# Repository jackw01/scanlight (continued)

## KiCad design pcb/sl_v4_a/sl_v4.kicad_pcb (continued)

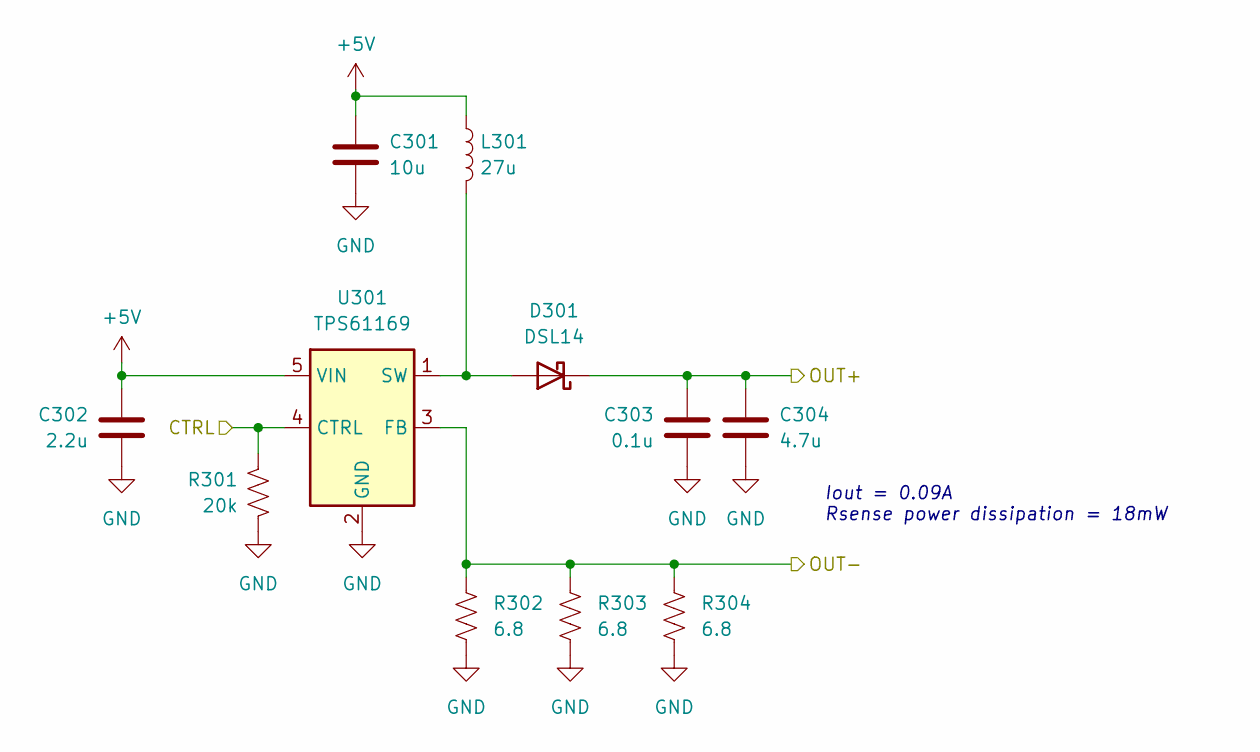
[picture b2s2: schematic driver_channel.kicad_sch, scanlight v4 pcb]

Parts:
C301: 10u; C_0805_2012Metric; MPN CL21A106KAYNNNE; LCSC C15850
C302: 2.2u; C_0402_1005Metric; MPN CL05A225MQ5NSNC; LCSC C12530
C303: 0.1u; C_0402_1005Metric; MPN CL05B104KB54PNC; LCSC C307331
C304: 4.7u; C_1206_3216Metric; MPN 1206B475K500NT; LCSC C29823
D301: DSL14; D_SOD-123F; MPN DSL14; LCSC C22466349
L301: 27u; L_Sunlord_SWPA6028S; MPN CR6028-270M; LCSC C7588756
R301: 20k; R_0402_1005Metric; MPN 0402WGF2002TCE; LCSC C25765
R302, R303, R304: 6.8; R_0402_1005Metric; MPN AC0402FR-076R8L; LCSC C227211
U301: TPS61169; SOT-353_SC-70-5; MPN TPS61169DCKR; LCSC C71045

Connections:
+5V: C301.1, C302.1, L301.1, U301.5 (VIN); also elsewhere on the board
/R1: R301.1, U301.4 (CTRL); also elsewhere on the board
/R1+: C303.1, C304.1, D301.1 (K); also elsewhere on the board
/R1-: R302.1, R303.1, R304.1, U301.3 (FB); also elsewhere on the board
GND: C301.2, C302.2, C303.2, C304.2, R301.2, R302.2, R303.2, R304.2, U301.2 (GND); also elsewhere on the board
unnamed: D301.2 (A), L301.2, U301.1 (SW)

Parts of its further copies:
C401, C501, C601: 10u; C_0805_2012Metric; MPN CL21A106KAYNNNE; LCSC C15850
C402, C502, C602: 2.2u; C_0402_1005Metric; MPN CL05A225MQ5NSNC; LCSC C12530
C403, C503, C603: 0.1u; C_0402_1005Metric; MPN CL05B104KB54PNC; LCSC C307331
C404, C504, C604: 4.7u; C_1206_3216Metric; MPN 1206B475K500NT; LCSC C29823
D401, D501, D601: DSL14; D_SOD-123F; MPN DSL14; LCSC C22466349
L401, L501, L601: 27u; L_Sunlord_SWPA6028S; MPN CR6028-270M; LCSC C7588756
R401, R501, R601: 20k; R_0402_1005Metric; MPN 0402WGF2002TCE; LCSC C25765
R402, R403, R404, R502, R503, R504, R602, R603, R604: 6.8; R_0402_1005Metric; MPN AC0402FR-076R8L; LCSC C227211
U401, U501, U601: TPS61169; SOT-353_SC-70-5; MPN TPS61169DCKR; LCSC C71045

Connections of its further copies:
+5V: C401.1, C402.1, C501.1, C502.1, C601.1, C602.1, L401.1, L501.1, L601.1, U401.5 (VIN), U501.5 (VIN), U601.5 (VIN); also elsewhere on the board
/B1: R501.1, U501.4 (CTRL); also elsewhere on the board
/B1+: C503.1, C504.1, D501.1 (K); also elsewhere on the board
/B1-: R502.1, R503.1, R504.1, U501.3 (FB); also elsewhere on the board
/G1: R401.1, U401.4 (CTRL); also elsewhere on the board
/G1+: C403.1, C404.1, D401.1 (K); also elsewhere on the board
/G1-: R402.1, R403.1, R404.1, U401.3 (FB); also elsewhere on the board
/W1: R601.1, U601.4 (CTRL); also elsewhere on the board
/W1+: C603.1, C604.1, D601.1 (K); also elsewhere on the board
/W1-: R602.1, R603.1, R604.1, U601.3 (FB); also elsewhere on the board
GND: C401.2, C402.2, C403.2, C404.2, C501.2, C502.2, C503.2, C504.2, C601.2, C602.2, C603.2, C604.2, R401.2, R402.2, R403.2, R404.2, R501.2, R502.2, R503.2, R504.2, R601.2, R602.2, R603.2, R604.2, U401.2 (GND), U501.2 (GND), U601.2 (GND); also elsewhere on the board
unnamed: D401.2 (A), L401.2, U401.1 (SW)
unnamed: D501.2 (A), L501.2, U501.1 (SW)
unnamed: D601.2 (A), L601.2, U601.1 (SW)

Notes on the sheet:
Iout = 0.09A Rsense power dissipation = 18mW

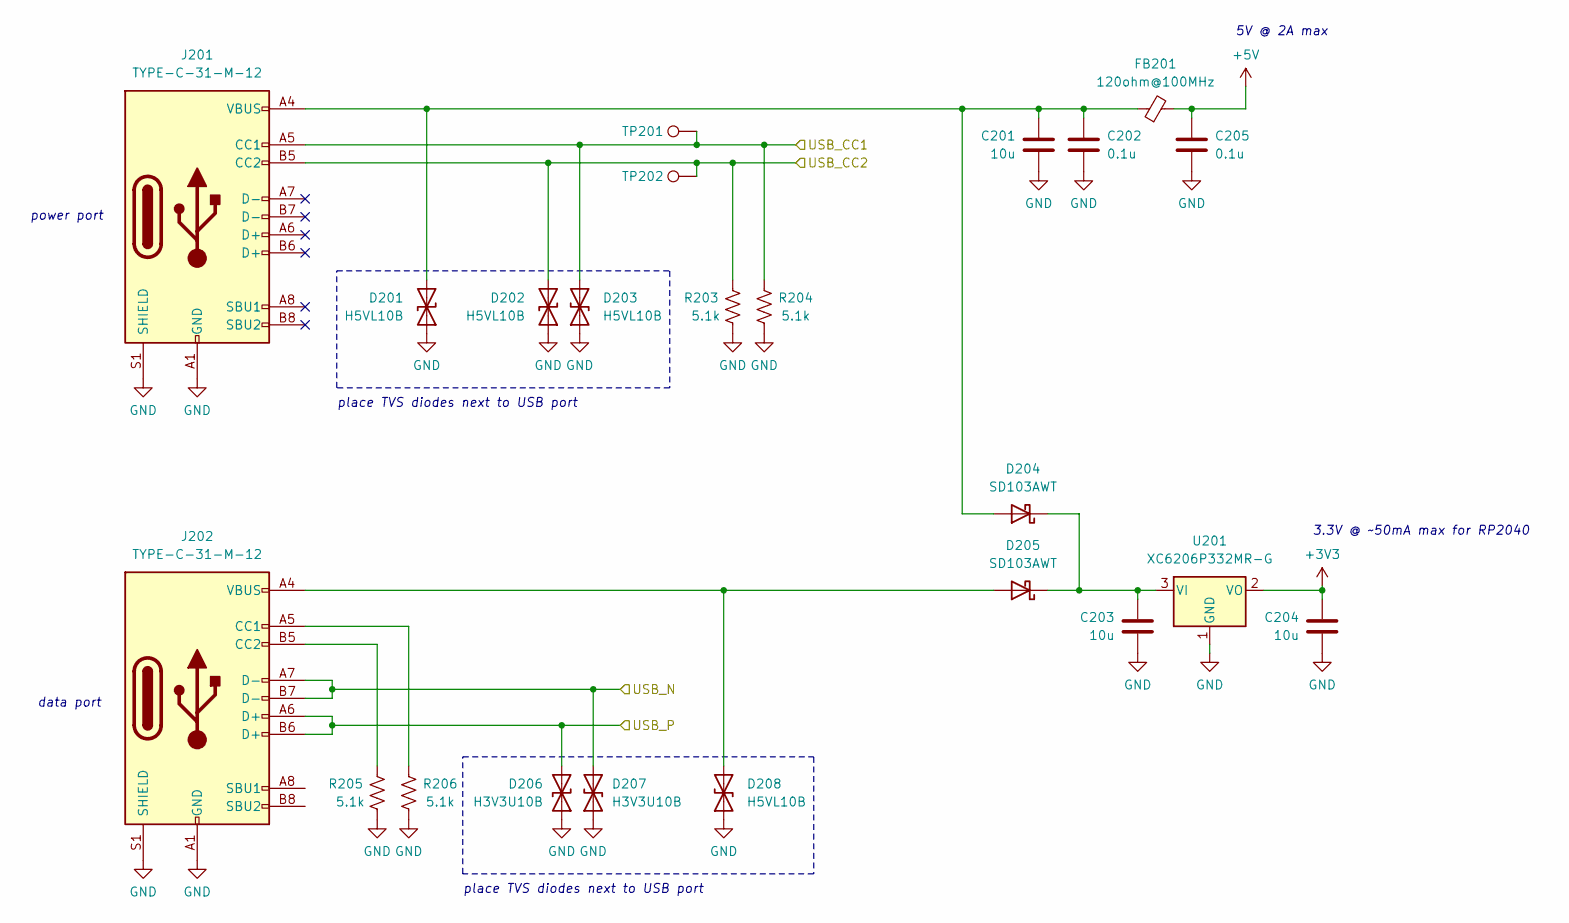
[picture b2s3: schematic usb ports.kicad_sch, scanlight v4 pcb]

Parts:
C201, C203, C204: 10u; C_0805_2012Metric; MPN CL21A106KAYNNNE; LCSC C15850
C202, C205: 0.1u; C_0402_1005Metric; MPN CL05B104KB54PNC; LCSC C307331
D201, D202, D203, D208: H5VL10B; D_SOD-882; MPN H5VL10B; LCSC C7420372
D204, D205: SD103AWT; D_SOD-523; MPN SD103AWT; LCSC C22466357
D206, D207: H3V3U10B; D_SOD-882; MPN H3V3U10B; LCSC C20615782
FB201: 120ohm@100MHz; L_0805_2012Metric; MPN UPZ2012E121-4R0TF; LCSC C97001
J201, J202: TYPE-C-31-M-12; USB_C_Receptacle_HRO_TYPE-C-31-M-12; MPN TYPE-C-31-M-12; LCSC C165948
R203, R204, R205, R206: 5.1k; R_0402_1005Metric; MPN 0402WGF5101TCE; LCSC C25905
TP201, TP202: TestPoint; TestPoint_Pad_D1.0mm
U201: XC6206P332MR-G; SOT-23-3; MPN XC6206P332MR-G; LCSC C5446

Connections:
+3V3: C204.1, U201.2 (VO); also elsewhere on the board
+5V: C205.1, FB201.2; also elsewhere on the board
/CC1: D203.2 (A2), J201.A5 (CC1), R204.1, TP201.1 (1_1); also elsewhere on the board
/CC2: D202.2 (A2), J201.B5 (CC2), R203.2, TP202.1 (1_1); also elsewhere on the board
/usb ports/USB_N: D207.2 (A2), J202.A7 (D-), J202.B7 (D-); also elsewhere on the board
/usb ports/USB_P: D206.2 (A2), J202.A6 (D+), J202.B6 (D+); also elsewhere on the board
GND: C201.2, C202.2, C203.2, C204.2, C205.2, D201.1 (A1), D202.1 (A1), D203.1 (A1), D206.1 (A1), D207.1 (A1), D208.1 (A1), J201.A1 (GND), J201.A12 (GND), J201.B1 (GND), J201.B12 (GND), J201.S1 (SHIELD), J202.A1 (GND), J202.A12 (GND), J202.B1 (GND), J202.B12 (GND), J202.S1 (SHIELD), R203.1, R204.2, R205.1, R206.2, U201.1 (GND); also elsewhere on the board
unnamed: C201.1, C202.1, D201.2 (A2), D204.2 (A), FB201.1, J201.A4 (VBUS), J201.A9 (VBUS), J201.B4 (VBUS), J201.B9 (VBUS)
unnamed: C203.1, D204.1 (K), D205.1 (K), U201.3 (VI)
unnamed: D205.2 (A), D208.2 (A2), J202.A4 (VBUS), J202.A9 (VBUS), J202.B4 (VBUS), J202.B9 (VBUS)
unnamed: J202.A5 (CC1), R206.1
unnamed: J202.B5 (CC2), R205.2

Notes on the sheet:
place TVS diodes next to USB port
power port
5V @ 2A max
3.3V @ ~50mA max for RP2040
data port

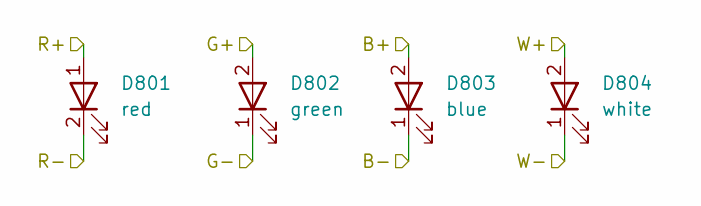
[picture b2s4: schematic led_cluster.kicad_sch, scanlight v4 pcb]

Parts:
D801: red; LED_2835_Reversed_Red_compact; MPN HL-AS-2835D15FC-S1-08-PCT-ZW-P6; LCSC C49435764
D802: green; LED_2835_compact; MPN TJ-S2835UG5W8TLC2G-A5; LCSC C440451
D803: blue; LED_2835_compact; MPN TJ-S2835UG5W8TLC6B-A5; LCSC C440452
D804: white; LED_2835_compact; MPN HL-AM-2835H421W-S1-08-HR6(SDCM<6)(4750K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; LCSC C516133

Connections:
/B1+: D803.2 (A); also elsewhere on the board
/G1+: D802.2 (A); also elsewhere on the board
/LED array/LED Cluster 0/B-: D803.1 (K); also elsewhere on the board
/LED array/LED Cluster 0/G-: D802.1 (K); also elsewhere on the board
/LED array/LED Cluster 0/R-: D801.2 (K); also elsewhere on the board
/LED array/LED Cluster 0/W-: D804.1 (K); also elsewhere on the board
/R1+: D801.1 (A); also elsewhere on the board
/W1+: D804.2 (A); also elsewhere on the board

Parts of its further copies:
D901, D1001, D1101, D1201, D1301, D1401, D1501, D1601: red; LED_2835_Reversed_Red_compact; MPN HL-AS-2835D15FC-S1-08-PCT-ZW-P6; LCSC C49435764
D902, D1002, D1102, D1202, D1302, D1402, D1502, D1602: green; LED_2835_compact; MPN TJ-S2835UG5W8TLC2G-A5; LCSC C440451
D903, D1003, D1103, D1203, D1303, D1403, D1503, D1603: blue; LED_2835_compact; MPN TJ-S2835UG5W8TLC6B-A5; LCSC C440452
D904, D1004, D1104, D1204, D1304, D1404, D1504, D1604: white; LED_2835_compact; MPN HL-AM-2835H421W-S1-08-HR6(SDCM<6)(4750K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; LCSC C516133

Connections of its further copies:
/B1-: D1603.1 (K); also elsewhere on the board
/G1-: D1602.1 (K); also elsewhere on the board
/LED array/LED Cluster 0/B-: D903.2 (A); also elsewhere on the board
/LED array/LED Cluster 0/G-: D902.2 (A); also elsewhere on the board
/LED array/LED Cluster 0/R-: D901.1 (A); also elsewhere on the board
/LED array/LED Cluster 0/W-: D904.2 (A); also elsewhere on the board
/LED array/LED Cluster 1/B-: D903.1 (K), D1003.2 (A)
/LED array/LED Cluster 1/G-: D902.1 (K), D1002.2 (A)
/LED array/LED Cluster 1/R-: D901.2 (K), D1001.1 (A)
/LED array/LED Cluster 1/W-: D904.1 (K), D1004.2 (A)
/LED array/LED Cluster 2/B-: D1003.1 (K), D1103.2 (A)
/LED array/LED Cluster 2/G-: D1002.1 (K), D1102.2 (A)
/LED array/LED Cluster 2/R-: D1001.2 (K), D1101.1 (A)
/LED array/LED Cluster 2/W-: D1004.1 (K), D1104.2 (A)
/LED array/LED Cluster 3/B-: D1103.1 (K), D1203.2 (A)
/LED array/LED Cluster 3/G-: D1102.1 (K), D1202.2 (A)
/LED array/LED Cluster 3/R-: D1101.2 (K), D1201.1 (A)
/LED array/LED Cluster 3/W-: D1104.1 (K), D1204.2 (A)
/LED array/LED Cluster 4/B-: D1203.1 (K), D1303.2 (A)
/LED array/LED Cluster 4/G-: D1202.1 (K), D1302.2 (A)
/LED array/LED Cluster 4/R-: D1201.2 (K), D1301.1 (A)
/LED array/LED Cluster 4/W-: D1204.1 (K), D1304.2 (A)
/LED array/LED Cluster 5/B-: D1303.1 (K), D1403.2 (A)
/LED array/LED Cluster 5/G-: D1302.1 (K), D1402.2 (A)
/LED array/LED Cluster 5/R-: D1301.2 (K), D1401.1 (A)
/LED array/LED Cluster 5/W-: D1304.1 (K), D1404.2 (A)
/LED array/LED Cluster 6/B-: D1403.1 (K), D1503.2 (A)
/LED array/LED Cluster 6/G-: D1402.1 (K), D1502.2 (A)
/LED array/LED Cluster 6/R-: D1401.2 (K), D1501.1 (A)
/LED array/LED Cluster 6/W-: D1404.1 (K), D1504.2 (A)
/LED array/LED Cluster 7/B-: D1503.1 (K), D1603.2 (A)
/LED array/LED Cluster 7/G-: D1502.1 (K), D1602.2 (A)
/LED array/LED Cluster 7/R-: D1501.2 (K), D1601.1 (A)
/LED array/LED Cluster 7/W-: D1504.1 (K), D1604.2 (A)
/R1-: D1601.2 (K); also elsewhere on the board
/W1-: D1604.1 (K); also elsewhere on the board

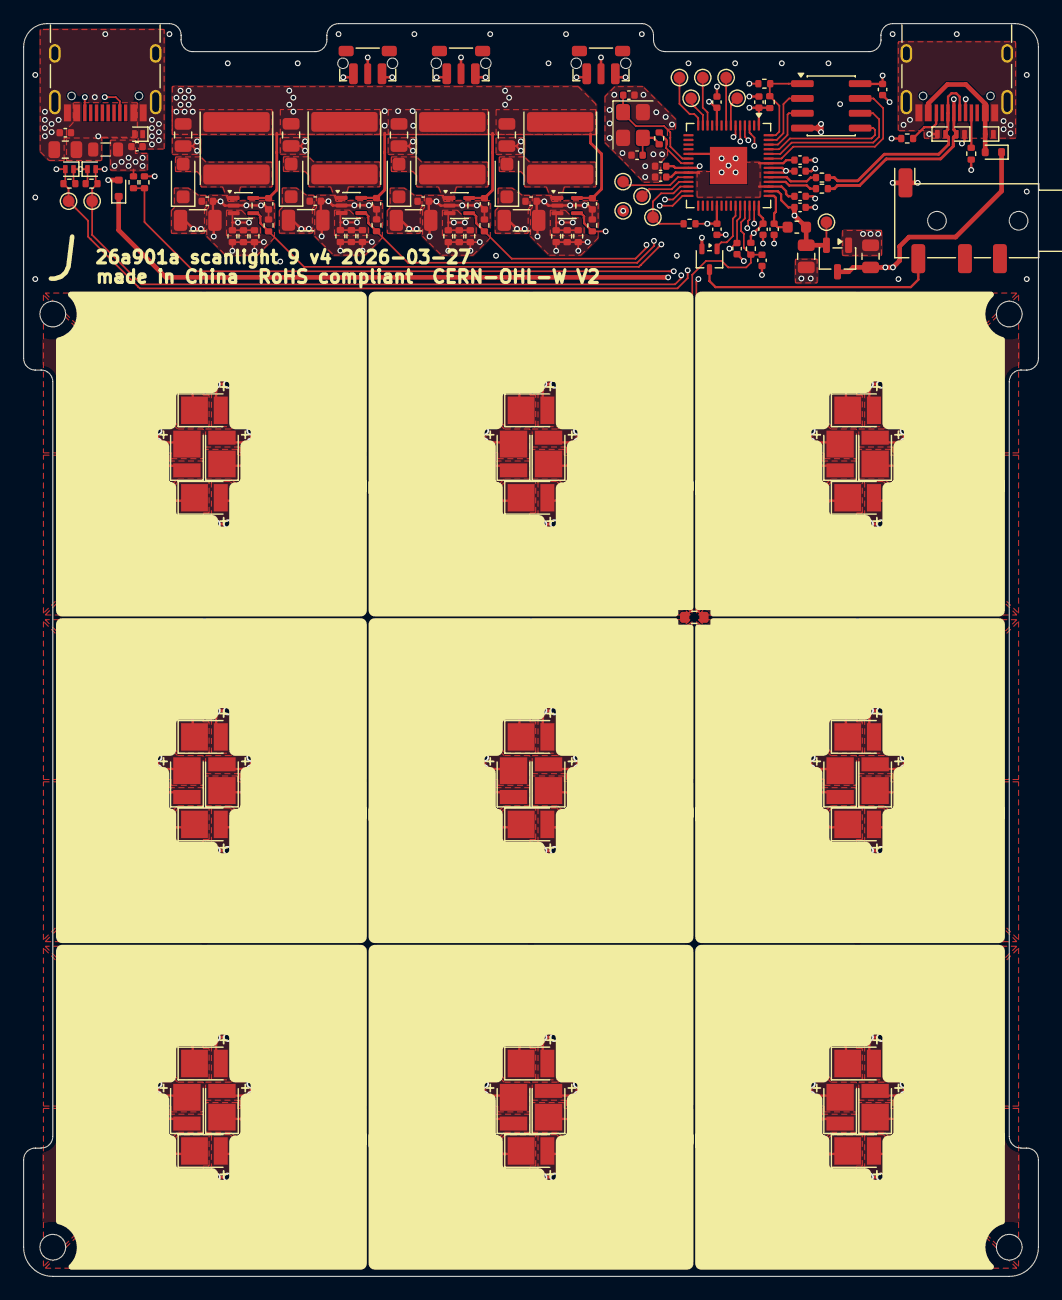
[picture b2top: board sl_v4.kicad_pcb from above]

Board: 4 copper layers, 87.0 x 107.4 mm, 152 parts (0 on the bottom side), 88 nets.

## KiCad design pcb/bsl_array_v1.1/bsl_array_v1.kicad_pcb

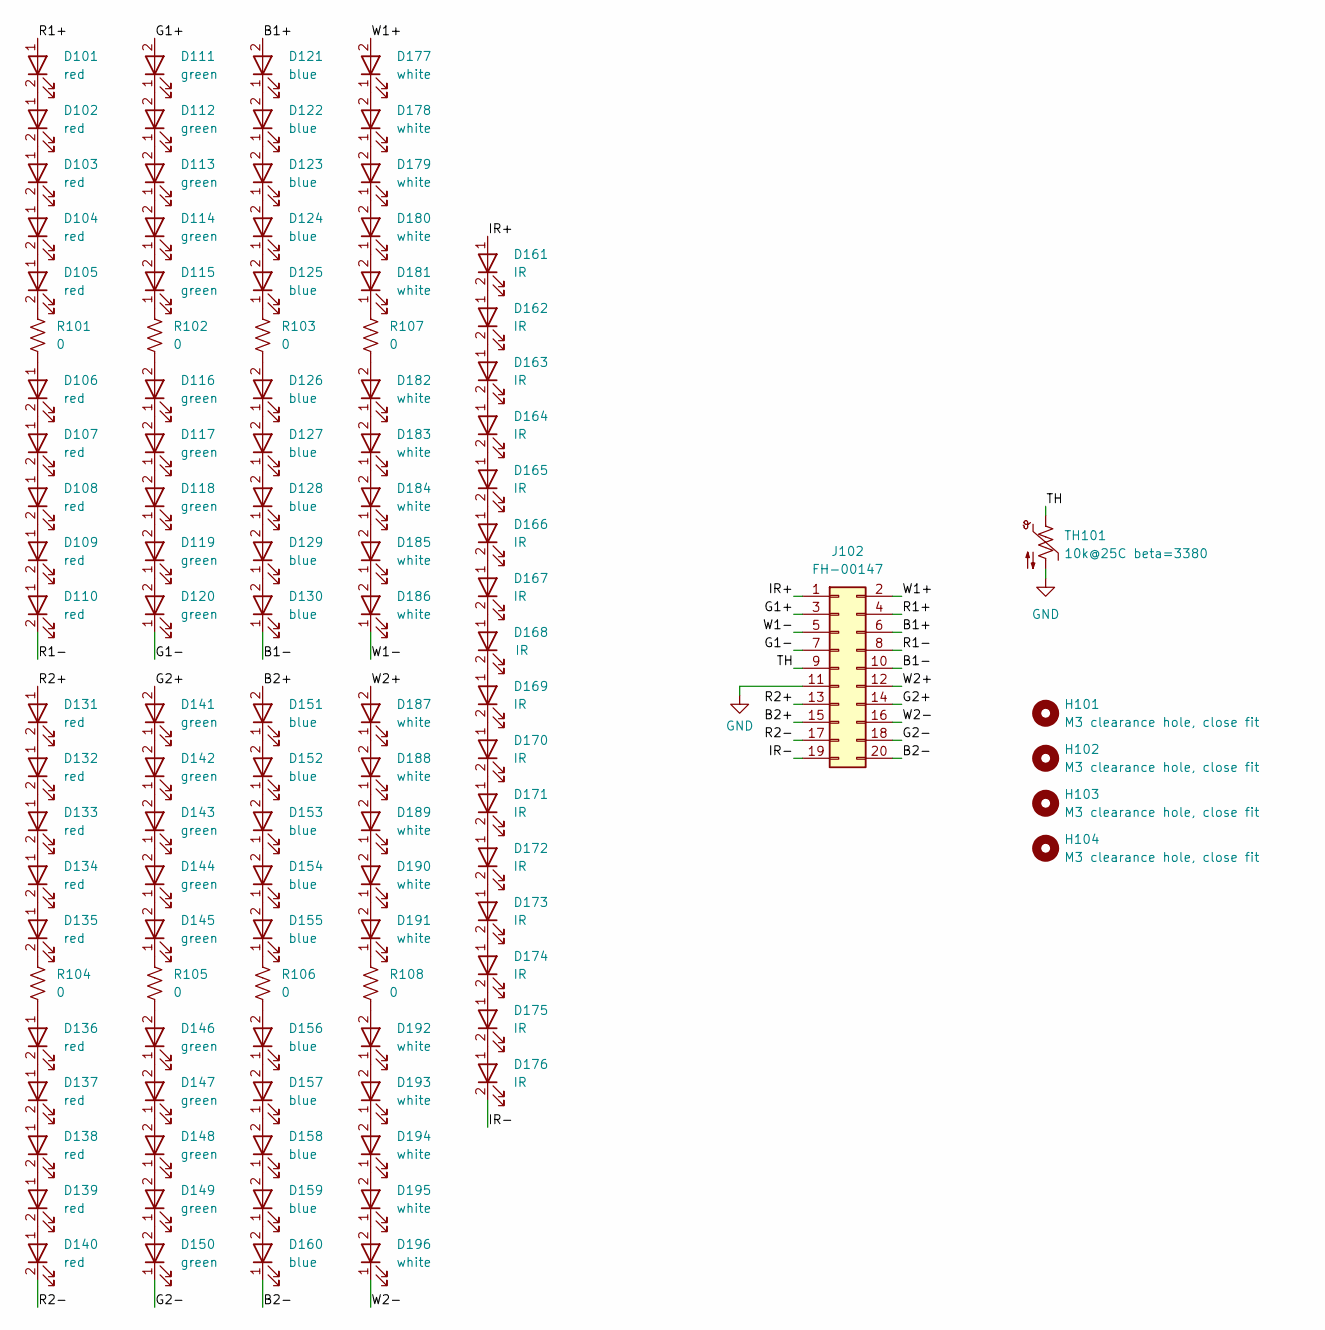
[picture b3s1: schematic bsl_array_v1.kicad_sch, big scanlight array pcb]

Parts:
D101, D102, D103, D104, D105, D106, D107, D108, D109, D110, D131, D132, D133, D134, D135, D136, D137, D138, D139, D140: red; LED_2835_Reversed_Red; MPN HL-AS-2835D15FC-S1-08-PCT-ZW-P6; LCSC C49435764
D111, D112, D113, D114, D115, D116, D117, D118, D119, D120, D141, D142, D143, D144, D145, D146, D147, D148, D149, D150: green; LED_2835; MPN TJ-S2835UG5W8TLC2G-A5; LCSC C440451
D121, D122, D123, D124, D125, D126, D127, D128, D129, D130, D151, D152, D153, D154, D155, D156, D157, D158, D159, D160: blue; LED_2835; MPN TJ-S2835UG5W8TLC6B-A5; LCSC C440452
D161, D162, D163, D164, D165, D166, D167, D168, D169, D170, D171, D172, D173, D174, D175, D176: IR; LED_2835_Reversed_Red; MPN P2835P1IRS7G12 850nm; LCSC C22466172
D177, D178, D179, D180, D181, D182, D183, D184, D185, D186, D187, D188, D189, D190, D191, D192, D193, D194, D195, D196: white; LED_2835; MPN HL-AM-2835H421W-S1-08-HR6(SDCM<6)(4750K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; LCSC C516133
H101, H102, H103, H104: M3 clearance hole, close fit; MountingHole_3.2mm_M3_Mask
J102: FH-00147; PinSocket_2x10_P2.00mm_Vertical_SMD; MPN FH-00147; LCSC C2685091
R101, R102, R103, R104, R105, R106, R107, R108: 0; R_1206_3216Metric; MPN 1206W4F0000T5E; LCSC C17888
TH101: 10k@25C beta=3380; R_0603_1608Metric; MPN NCP18XH103F03RB; LCSC C13564

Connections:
/B1+: D121.2 (A), J102.6
/B1-: D130.1 (K), J102.10
/B2+: D151.2 (A), J102.15
/B2-: D160.1 (K), J102.20
/G1+: D111.2 (A), J102.3
/G1-: D120.1 (K), J102.7
/G2+: D141.2 (A), J102.14
/G2-: D150.1 (K), J102.18
/IR+: D161.1 (A), J102.1
/IR-: D176.2 (K), J102.19
/R1+: D101.1 (A), J102.4
/R1-: D110.2 (K), J102.8
/R2+: D131.1 (A), J102.13
/R2-: D140.2 (K), J102.17
/TH: J102.9, TH101.1
/W1+: D177.2 (A), J102.2
/W1-: D186.1 (K), J102.5
/W2+: D187.2 (A), J102.12
/W2-: D196.1 (K), J102.16
GND: J102.11, TH101.2
unnamed: D101.2 (K), D102.1 (A)
unnamed: D102.2 (K), D103.1 (A)
unnamed: D103.2 (K), D104.1 (A)
unnamed: D104.2 (K), D105.1 (A)
unnamed: D105.2 (K), R101.1
unnamed: D106.1 (A), R101.2
unnamed: D106.2 (K), D107.1 (A)
unnamed: D107.2 (K), D108.1 (A)
unnamed: D108.2 (K), D109.1 (A)
unnamed: D109.2 (K), D110.1 (A)
unnamed: D111.1 (K), D112.2 (A)
unnamed: D112.1 (K), D113.2 (A)
unnamed: D113.1 (K), D114.2 (A)
unnamed: D114.1 (K), D115.2 (A)
unnamed: D115.1 (K), R102.1
unnamed: D116.2 (A), R102.2
unnamed: D116.1 (K), D117.2 (A)
unnamed: D117.1 (K), D118.2 (A)
unnamed: D118.1 (K), D119.2 (A)
unnamed: D119.1 (K), D120.2 (A)
unnamed: D121.1 (K), D122.2 (A)
unnamed: D122.1 (K), D123.2 (A)
unnamed: D123.1 (K), D124.2 (A)
unnamed: D124.1 (K), D125.2 (A)
unnamed: D125.1 (K), R103.1
unnamed: D126.2 (A), R103.2
unnamed: D126.1 (K), D127.2 (A)
unnamed: D127.1 (K), D128.2 (A)
unnamed: D128.1 (K), D129.2 (A)
unnamed: D129.1 (K), D130.2 (A)
unnamed: D131.2 (K), D132.1 (A)
unnamed: D132.2 (K), D133.1 (A)
unnamed: D133.2 (K), D134.1 (A)
unnamed: D134.2 (K), D135.1 (A)
unnamed: D135.2 (K), R104.1
unnamed: D136.1 (A), R104.2
unnamed: D136.2 (K), D137.1 (A)
unnamed: D137.2 (K), D138.1 (A)
unnamed: D138.2 (K), D139.1 (A)
unnamed: D139.2 (K), D140.1 (A)
unnamed: D141.1 (K), D142.2 (A)
unnamed: D142.1 (K), D143.2 (A)
unnamed: D143.1 (K), D144.2 (A)
unnamed: D144.1 (K), D145.2 (A)
unnamed: D145.1 (K), R105.1
unnamed: D146.2 (A), R105.2
unnamed: D146.1 (K), D147.2 (A)
unnamed: D147.1 (K), D148.2 (A)
unnamed: D148.1 (K), D149.2 (A)
unnamed: D149.1 (K), D150.2 (A)
unnamed: D151.1 (K), D152.2 (A)
unnamed: D152.1 (K), D153.2 (A)
unnamed: D153.1 (K), D154.2 (A)
unnamed: D154.1 (K), D155.2 (A)
unnamed: D155.1 (K), R106.1
unnamed: D156.2 (A), R106.2
unnamed: D156.1 (K), D157.2 (A)
unnamed: D157.1 (K), D158.2 (A)
unnamed: D158.1 (K), D159.2 (A)
unnamed: D159.1 (K), D160.2 (A)
unnamed: D161.2 (K), D162.1 (A)
unnamed: D162.2 (K), D163.1 (A)
unnamed: D163.2 (K), D164.1 (A)
unnamed: D164.2 (K), D165.1 (A)
unnamed: D165.2 (K), D166.1 (A)
unnamed: D166.2 (K), D167.1 (A)
unnamed: D167.2 (K), D168.1 (A)
unnamed: D168.2 (K), D169.1 (A)
unnamed: D169.2 (K), D170.1 (A)
unnamed: D170.2 (K), D171.1 (A)
unnamed: D171.2 (K), D172.1 (A)
unnamed: D172.2 (K), D173.1 (A)
unnamed: D173.2 (K), D174.1 (A)
unnamed: D174.2 (K), D175.1 (A)
unnamed: D175.2 (K), D176.1 (A)
unnamed: D177.1 (K), D178.2 (A)
unnamed: D178.1 (K), D179.2 (A)
unnamed: D179.1 (K), D180.2 (A)
unnamed: D180.1 (K), D181.2 (A)
unnamed: D181.1 (K), R107.1
unnamed: D182.2 (A), R107.2
unnamed: D182.1 (K), D183.2 (A)
unnamed: D183.1 (K), D184.2 (A)
unnamed: D184.1 (K), D185.2 (A)
unnamed: D185.1 (K), D186.2 (A)
unnamed: D187.1 (K), D188.2 (A)
unnamed: D188.1 (K), D189.2 (A)
unnamed: D189.1 (K), D190.2 (A)
unnamed: D190.1 (K), D191.2 (A)
unnamed: D191.1 (K), R108.1
unnamed: D192.2 (A), R108.2
unnamed: D192.1 (K), D193.2 (A)
unnamed: D193.1 (K), D194.2 (A)
unnamed: D194.1 (K), D195.2 (A)
unnamed: D195.1 (K), D196.2 (A)

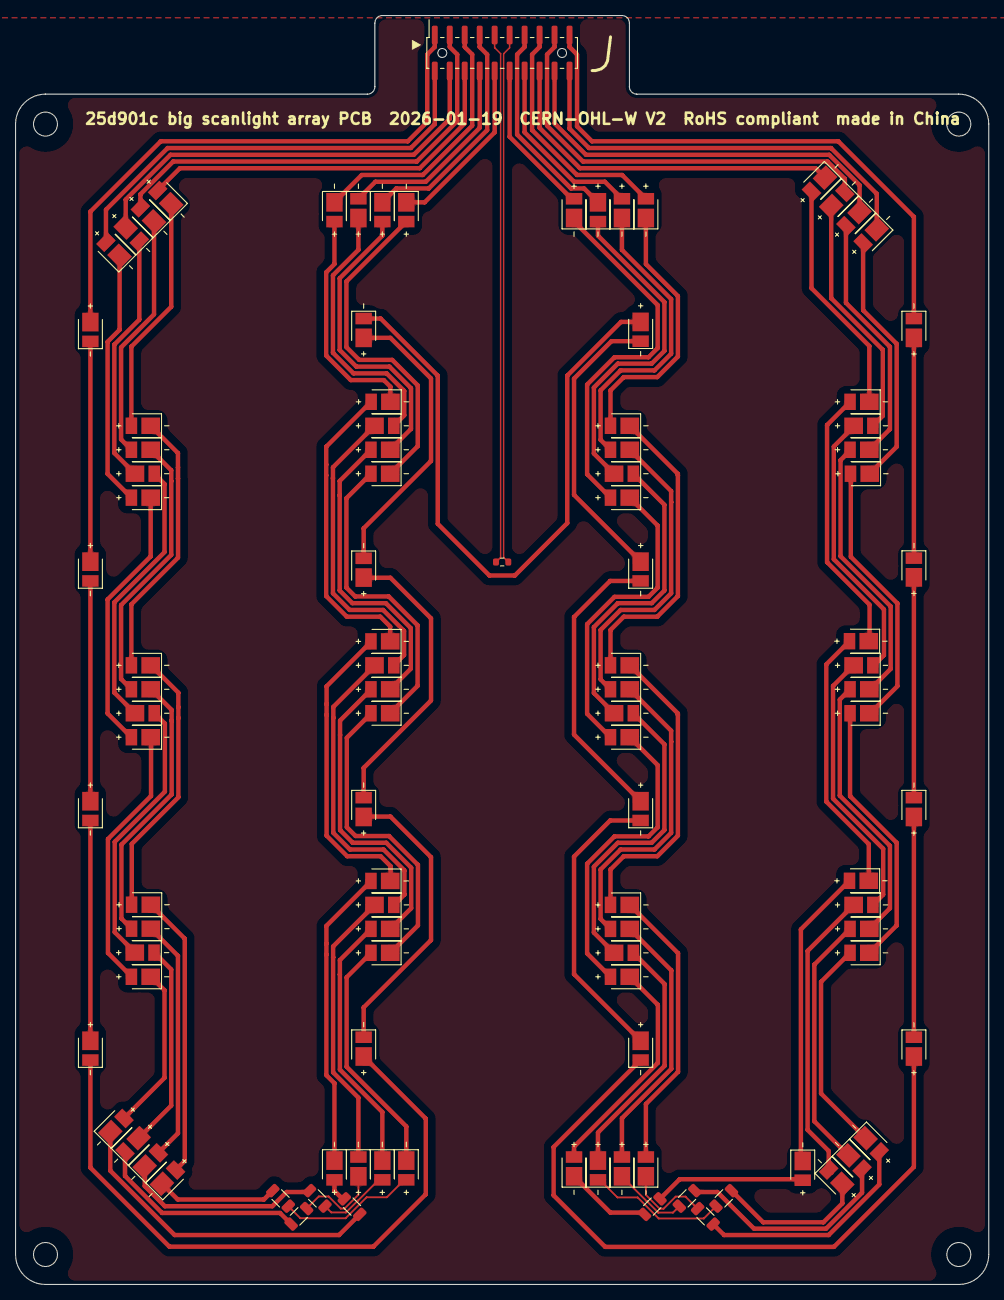
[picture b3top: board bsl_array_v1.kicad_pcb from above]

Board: 2 copper layers, 130.0 x 169.5 mm, 110 parts (0 on the bottom side), 115 nets.

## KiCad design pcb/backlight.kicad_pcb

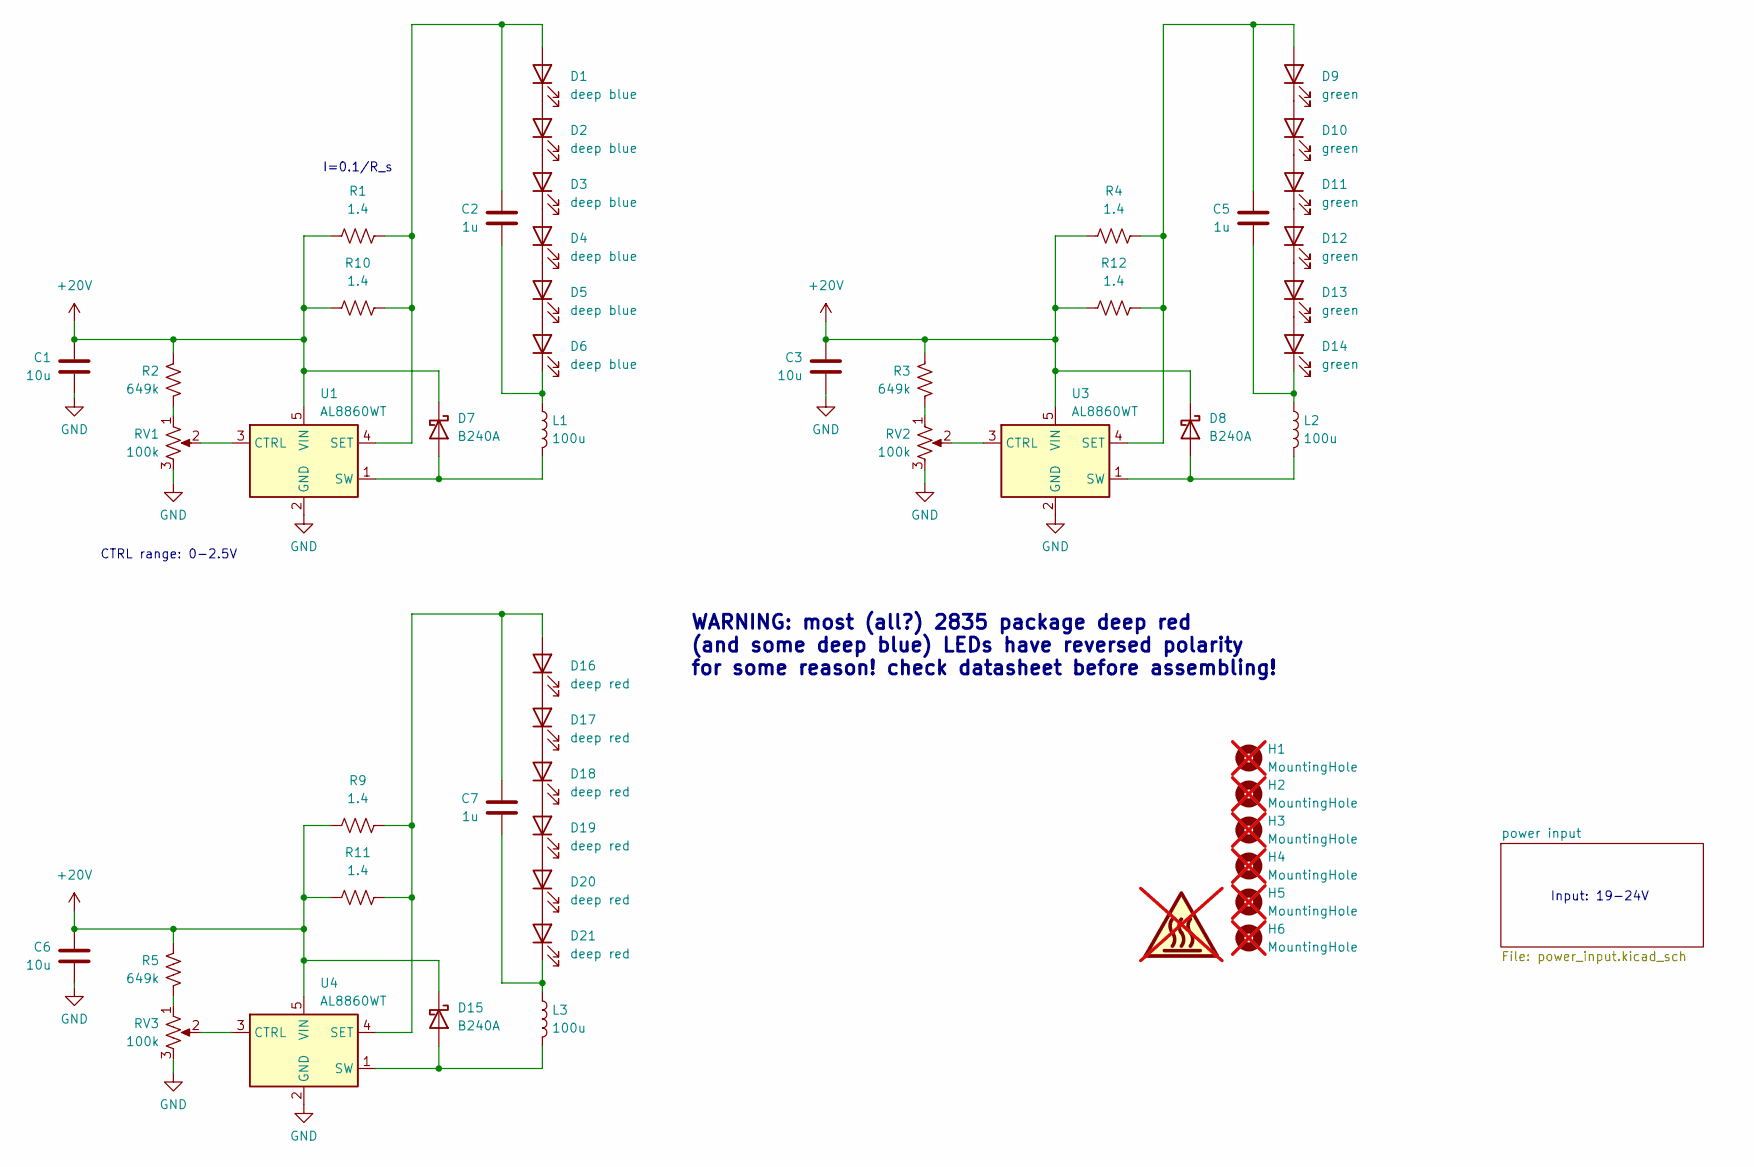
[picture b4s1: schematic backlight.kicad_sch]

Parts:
C1, C3, C6: 10u; C_1210_3225Metric; MPN Generic 10uF 50V 1210 X7R
C2, C5, C7: 1u; C_0603_1608Metric; MPN Generic 1uF 25V 0603 X7R
D1, D2, D3, D4, D5, D6: deep blue; LED_PLCC_2835_Handsoldering; MPN JE2835ARY-N-0002A0000-N0000001
D7, D8, D15: B240A; D_SMA; MPN B240A-13-F
D9, D10, D11, D12, D13, D14: green; LED_PLCC_2835_Handsoldering; MPN JE2835AGR-N-0002A0000-N0000001
D16, D17, D18, D19, D20, D21: deep red; LED_PLCC_2835_Handsoldering; MPN 67-21S/NDR3C-P5080C1C51827Z15/2T
H1, H2, H3, H4, H5, H6: MountingHole; MountingHole_2.2mm_M2_Mask_5mm; not fitted
L1, L2, L3: 100u; L_Bourns_SRN8040TA; MPN HPC 8040NV-101M
R1, R4, R9, R10, R11, R12: 1.4; R_1206_3216Metric; MPN RK73H2ATTD1R40F
R2, R3, R5: 649k; R_0603_1608Metric; MPN Generic 649KOhm 0603 1%
RV1, RV2, RV3: 100k; Potentiometer_Bourns_PTV09A-1_Single_Vertical; MPN PTV09A-4020U-B104
SYM101: SYM_Hot_Large; hot-surface_1x; not fitted
U1, U3, U4: AL8860WT; TSOT-23-5; MPN AL8860WT-7

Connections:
+20V: C1.1, C3.1, C6.1, D7.1 (K), D8.1 (K), D15.1 (K), R1.1, R2.1, R3.1, R4.1, R5.1, R9.1, R10.1, R11.1, R12.1, U1.5 (VIN), U3.5 (VIN), U4.5 (VIN); also elsewhere on the board
GND: C1.2, C3.2, C6.2, RV1.3, RV2.3, RV3.3, U1.2 (GND), U3.2 (GND), U4.2 (GND); also elsewhere on the board
unnamed: C2.1, D1.2 (A), R1.2, R10.2, U1.4 (SET)
unnamed: D1.1 (K), D2.2 (A)
unnamed: D2.1 (K), D3.2 (A)
unnamed: D3.1 (K), D4.2 (A)
unnamed: D4.1 (K), D5.2 (A)
unnamed: D5.1 (K), D6.2 (A)
unnamed: C2.2, D6.1 (K), L1.1
unnamed: D7.2 (A), L1.2, U1.1 (SW)
unnamed: D8.2 (A), L2.2, U3.1 (SW)
unnamed: C5.1, D9.2 (A), R4.2, R12.2, U3.4 (SET)
unnamed: D9.1 (K), D10.2 (A)
unnamed: D10.1 (K), D11.2 (A)
unnamed: D11.1 (K), D12.2 (A)
unnamed: D12.1 (K), D13.2 (A)
unnamed: D13.1 (K), D14.2 (A)
unnamed: C5.2, D14.1 (K), L2.1
unnamed: D15.2 (A), L3.2, U4.1 (SW)
unnamed: C7.1, D16.1 (A), R9.2, R11.2, U4.4 (SET)
unnamed: D16.2 (K), D17.1 (A)
unnamed: D17.2 (K), D18.1 (A)
unnamed: D18.2 (K), D19.1 (A)
unnamed: D19.2 (K), D20.1 (A)
unnamed: D20.2 (K), D21.1 (A)
unnamed: C7.2, D21.2 (K), L3.1
unnamed: R2.2, RV1.1
unnamed: R3.2, RV2.1
unnamed: R5.2, RV3.1
unnamed: RV1.2, U1.3 (CTRL)
unnamed: RV2.2, U3.3 (CTRL)
unnamed: RV3.2, U4.3 (CTRL)

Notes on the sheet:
Input: 19-24V
CTRL range: 0-2.5V
I=0.1/R_s
WARNING: most (all?) 2835 package deep red (and some deep blue) LEDs have reversed polarity for some reason! check datasheet before assembling!

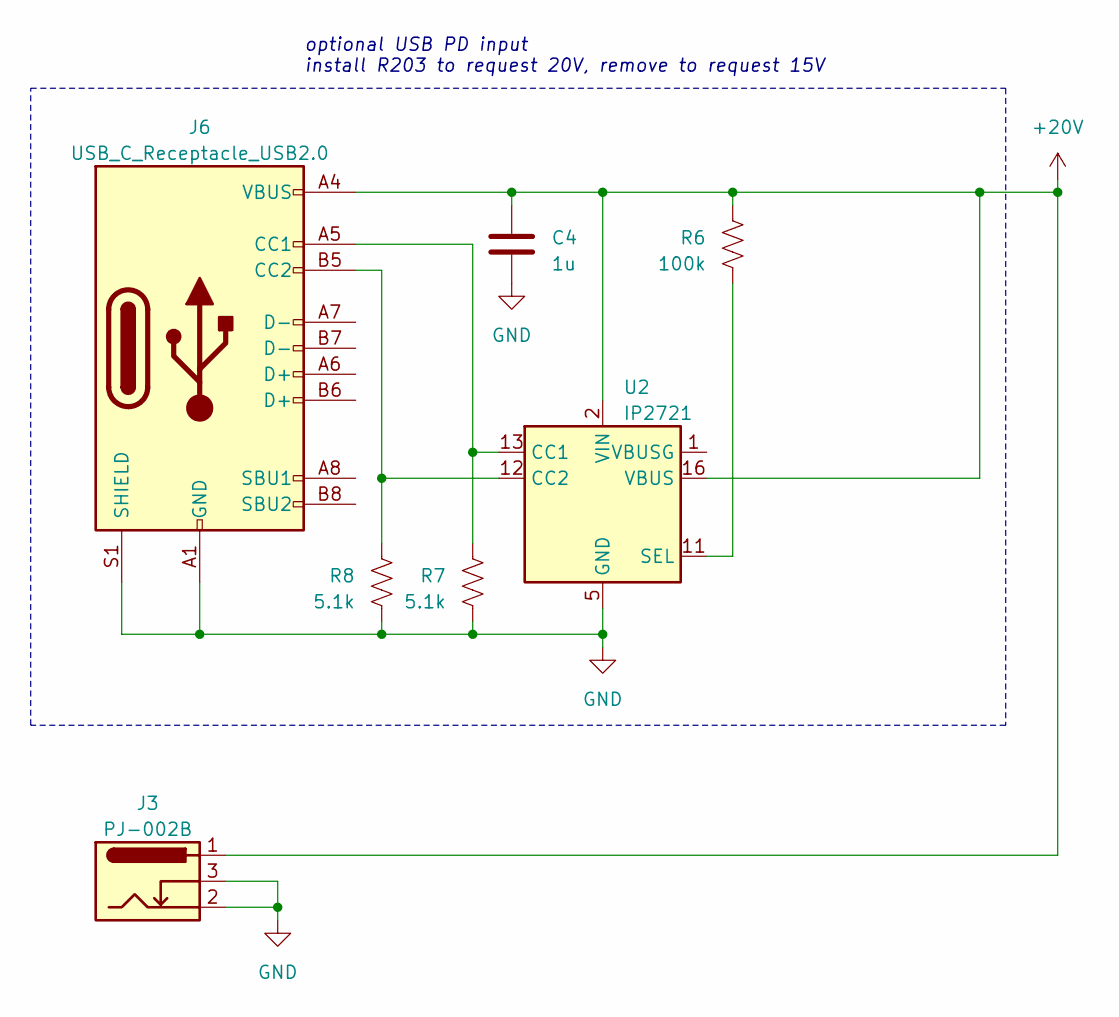
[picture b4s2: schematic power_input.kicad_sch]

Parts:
C4: 1u; C_0603_1608Metric; MPN Generic 1uF 25V 0603 X7R
J3: PJ-002B; BarrelJack_GCT_DCJ200-10-A_Horizontal; MPN PJ-002B
J6: USB_C_Receptacle_USB2.0; USB_C_Receptacle_GCT_USB4105-xx-A_16P_TopMnt_Horizontal; MPN USB4105-GF-A
R6: 100k; R_0603_1608Metric; MPN Generic 100KOhm 0603 5%
R7, R8: 5.1k; R_0603_1608Metric; MPN Generic 5.1KOhm 0603 5%
U2: IP2721; TSSOP-16_4.4x5mm_P0.65mm; MPN IP2721

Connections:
+20V: C4.2, J3.1, J6.A4 (VBUS), J6.A9 (VBUS), J6.B4 (VBUS), J6.B9 (VBUS), R6.1, U2.2 (VIN), U2.16 (VBUS); also elsewhere on the board
GND: C4.1, J3.2, J3.3, J6.A1 (GND), J6.A12 (GND), J6.B1 (GND), J6.B12 (GND), J6.S1 (SHIELD), R7.2, R8.2, U2.5 (GND); also elsewhere on the board
unnamed: J6.A5 (CC1), R7.1, U2.13 (CC1)
unnamed: J6.B5 (CC2), R8.1, U2.12 (CC2)
unnamed: R6.2, U2.11 (SEL)

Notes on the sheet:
optional USB PD input install R203 to request 20V, remove to request 15V

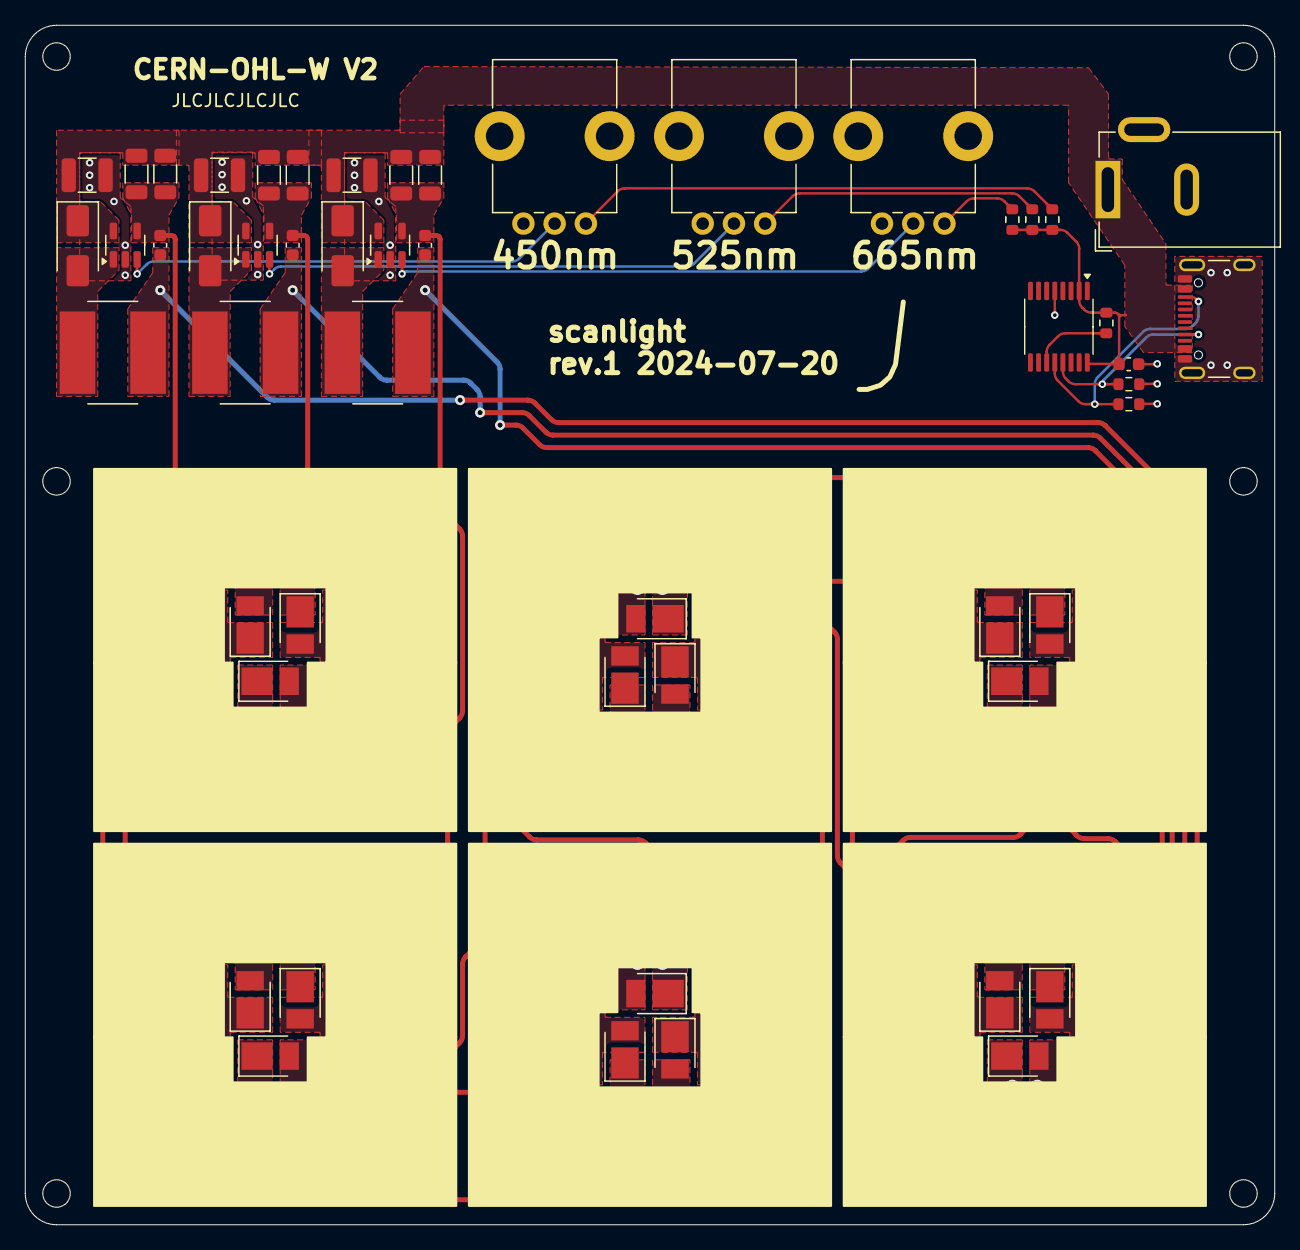
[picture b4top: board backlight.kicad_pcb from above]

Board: 2 copper layers, 100.0 x 96.0 mm, 59 parts (1 on the bottom side), 35 nets.

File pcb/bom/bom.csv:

Reference,Value,Footprint,Qty,DNP,MPN
"C1,C3,C6",10u,Capacitor_SMD:C_1210_3225Metric,3,,Generic 10uF 50V 1210 X7R
"C2,C4,C5,C7",1u,Capacitor_SMD:C_0603_1608Metric,4,,Generic 1uF 25V 0603 X7R
"D1,D2,D3,D4,D5,D6",deep blue,LED_SMD:LED_PLCC_2835_Handsoldering,6,,JE2835ARY-N-0002A0000-N0000001
"D7,D8,D15",B240A,Diode_SMD:D_SMA,3,,B240A-13-F
"D9,D10,D11,D12,D13,D14",green,LED_SMD:LED_PLCC_2835_Handsoldering,6,,JE2835AGR-N-0002A0000-N0000001
"D16,D17,D18,D19,D20,D21",deep red,LED_SMD:LED_PLCC_2835_Handsoldering,6,,67-21S/NDR3C-P5080C1C51827Z15/2T
"H1,H2,H3,H4,H5,H6",MountingHole,Custom:MountingHole_2.2mm_M2_Mask_5mm,6,,
J3,PJ-002B,Connector_BarrelJack:BarrelJack_GCT_DCJ200-10-A_Horizontal,1,,PJ-002B
J6,USB_C_Receptacle_USB2.0,Connector_USB:USB_C_Receptacle_GCT_USB4105-xx-A_16P_TopMnt_Horizontal,1,,USB4105-GF-A
"L1,L2,L3",100u,Inductor_SMD:L_Bourns_SRN8040TA,3,,HPC 8040NV-101M 
"R1,R4,R9,R10,R11,R12",1.4,Resistor_SMD:R_1206_3216Metric,6,,RK73H2ATTD1R40F
"R2,R3,R5",649k,Resistor_SMD:R_0603_1608Metric,3,,Generic 649KOhm 0603 1%
R6,100k,Resistor_SMD:R_0603_1608Metric,1,,Generic 100KOhm 0603 5%
"R7,R8",5.1k,Resistor_SMD:R_0603_1608Metric,2,,Generic 5.1KOhm 0603 5%
"RV1,RV2,RV3",100k,Potentiometer_THT:Potentiometer_Bourns_PTV09A-1_Single_Vertical,3,,PTV09A-4020U-B104
SYM101,SYM_Hot_Large,Custom:hot-surface_1x,1,,
"U1,U3,U4",AL8860WT,Package_TO_SOT_SMD:TSOT-23-5,3,,AL8860WT-7
U2,IP2721,Package_SO:TSSOP-16_4.4x5mm_P0.65mm,1,,IP2721
